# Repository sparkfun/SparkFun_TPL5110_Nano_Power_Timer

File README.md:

SparkFun TPL5110 Nano Power Timer
========================================

[*SparkFun Nano Power Switch (PRT-15353)*](https://www.sparkfun.com/products/15353)

Sometimes we want our projects on, but sometimes we want to turn them off for a while to save power. The SparkFun Nano Power Timer will run while only consuming minimal power (approximately 35nA) and turn your project on after a set amount of time. When you are done polling your sensors, posting data to the web, writing to your logger, or planning world domination, your microcontroller can tell the Nano Power Timer to turn off the power. No more running your microcontroller all day when you only want to read the ambient temperature once per hour.

Repository Contents
-------------------

* **/Documentation** - Data sheets, additional product information
* **/Firmware** - Example code 
* **/Hardware** - Eagle design files (.brd, .sch)
* **/Production** - Production panel files (.brd)

Documentation
--------------
* **[Hookup Guide](https://learn.sparkfun.com/tutorials/tpl5110-nano-power-timer-hookup-guide)** - Basic hookup guide for the TPL5110 Nano Power Timer.
* **[SparkFun Fritzing repo](https://github.com/sparkfun/Fritzing_Parts)** - Fritzing diagrams for SparkFun products.

License Information
-------------------
This product is _**open source**_! 

Please review the LICENSE.md file for license information. 

If you have any questions or concerns on licensing, please contact technical support on our [SparkFun forums](https://forum.sparkfun.com/viewforum.php?f=152).

Distributed as-is; no warranty is given.

- Your friends at SparkFun.

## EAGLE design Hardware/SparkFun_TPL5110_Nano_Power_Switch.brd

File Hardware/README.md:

SparkFun Nano Power Switch Design Files
=====================================

The .sch and .brd files hare are Eagle CAD schematic and PCB design files from SparkFun Electronics.
A freeware version of Eagle can be found [here](http://www.cadsoftusa.com/download-eagle/freeware/).

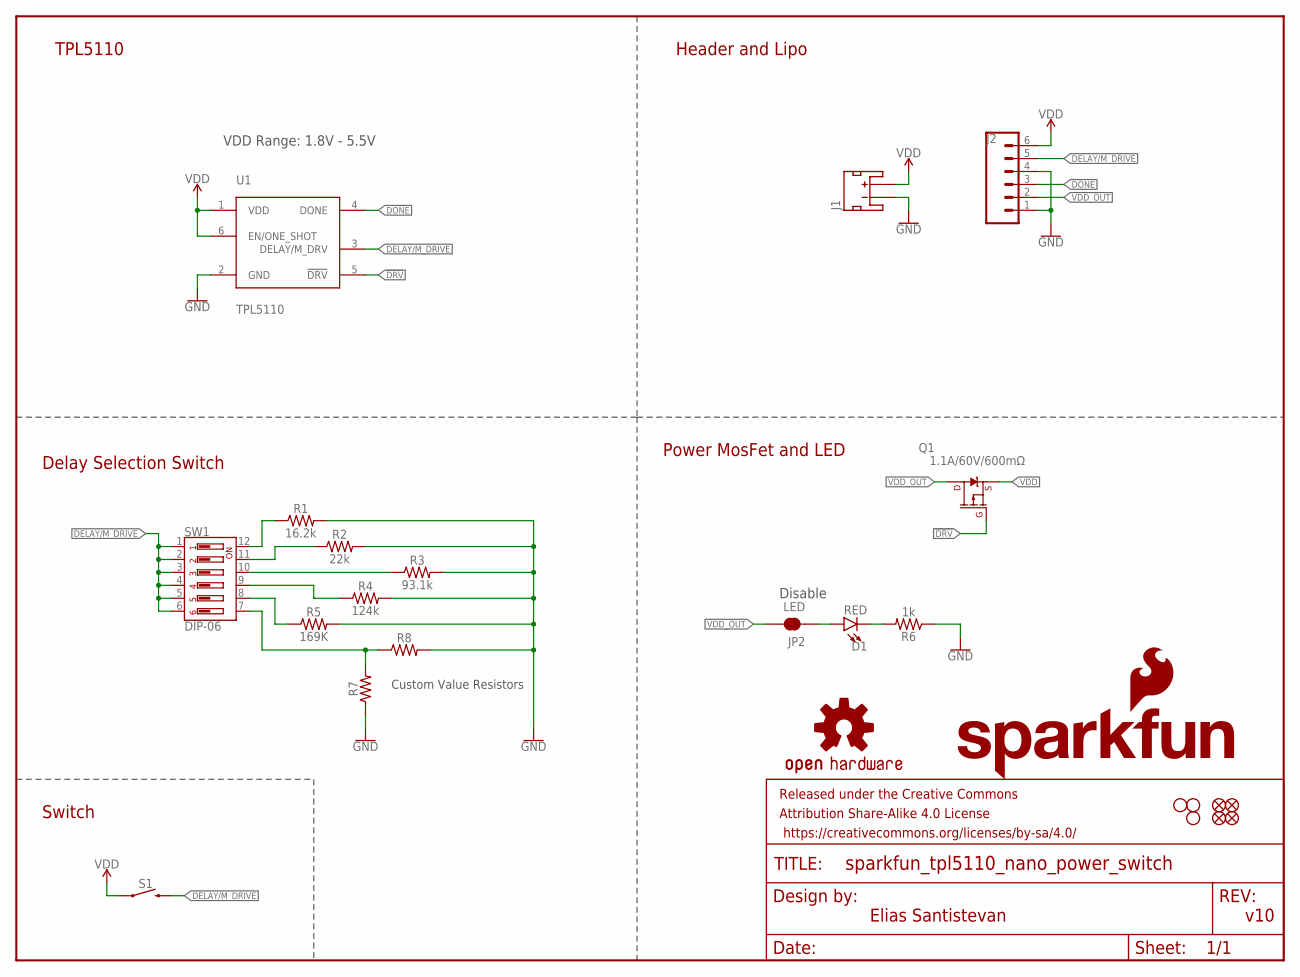
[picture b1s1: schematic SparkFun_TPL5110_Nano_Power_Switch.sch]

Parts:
D1: RED; LED-0603
FD1, FD2, FD3, FD4: FIDUCIALUFIDUCIAL; FIDUCIAL-MICRO
FRAME1: FRAME-LETTER; CREATIVE_COMMONS
H1, H2, H4: STAND-OFFTIGHT; STAND-OFF-TIGHT
J1: JST_2MM_MALE; JST-2-SMD
J2: CONN_06NO_SILK_NO_POP; 1X06_NO_SILK
JP2: LED; SMT-JUMPER_2_NC_TRACE_SILK
LOGO1: SFE_LOGO_NAME.1_INCH; SFE_LOGO_NAME_.1
LOGO2: OSHW-LOGOS; OSHW-LOGO-S
LOGO3: SFE_LOGO_FLAME.1_INCH; SFE_LOGO_FLAME_.1
Q1: 1.1A/60V/600mΩ; SOT23-3
R1: 16.2k; 0603
R2: 22k; 0603
R3: 93.1k; 0603
R4: 124k; 0603
R5: 169K; 0603
R6: 1k; 0603
R7: 0603
R8: AXIAL-0.3
S1: MOMENTARY-SWITCH-SPST-SMD-5.2MM-TALL; TACTILE_SWITCH_SMD_5.2MM
SW1: DIP-06; DIPSWITCH-06-SMD
U1: TPL5110; SOT23-6

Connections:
!DRV: Q1.1 (G), U1.5 (!DRV)
DELAY/M_DRIVE: J2.5, S1.3 (2), SW1.1, SW1.2, SW1.3, SW1.4, SW1.5, SW1.6, U1.3 (DELAY/M_DRV)
DONE: J2.3, U1.4 (DONE)
GND: J1.1 (-), J2.1, J2.4, R1.2, R2.2, R3.2, R4.2, R5.2, R6.1, R7.1, R8.P$2 (2), U1.2 (GND)
unnamed: D1.C, R6.2
unnamed: R1.1, SW1.12
unnamed: R2.1, SW1.11
unnamed: R3.1, SW1.10
unnamed: R4.1, SW1.9
unnamed: R5.1, SW1.8
unnamed: R7.2, R8.P$1 (1), SW1.7
unnamed: D1.A, JP2.1
VDD: J1.2 (+), J2.6, Q1.2 (S), S1.1, U1.1 (VDD), U1.6 (EN/ONE_SHOT)
VDD_OUT: J2.2, JP2.2, Q1.3 (D)

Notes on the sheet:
Elias Santistevan
v10
VDD Range: 1.8V - 5.5V
TPL5110
Header and Lipo
Power MosFet and LED
Delay Selection Switch
Switch
Disable
Custom Value Resistors

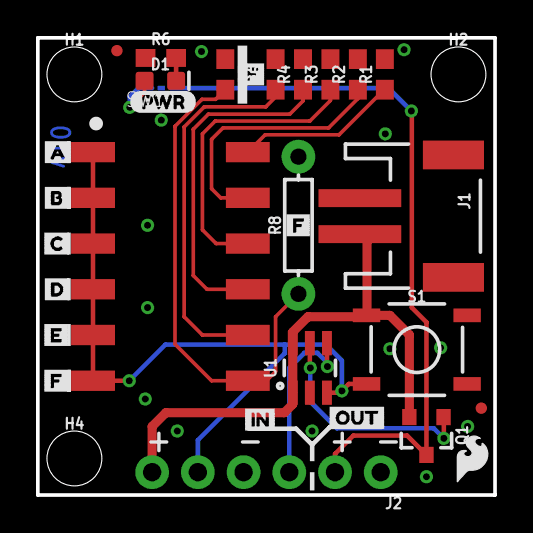
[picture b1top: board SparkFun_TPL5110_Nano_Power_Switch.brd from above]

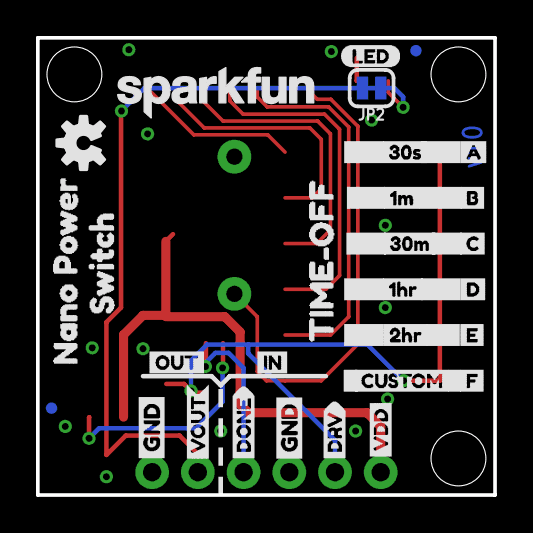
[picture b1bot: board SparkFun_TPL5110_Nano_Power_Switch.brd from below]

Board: 2 copper layers, 25.4 x 25.4 mm, 62 parts (29 on the bottom side), 14 nets.

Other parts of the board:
U$1: DONE0
U$2, U$4: GND-03
U$3: VOUT0
U$5: VDD0
U$6: NANO_POWER0
U$7: SWITCH0
U$8: 1M0
U$9: 30S4
U$10: 30M2
U$11: 1HR3
U$12: 2HR4
U$13: LED0
U$14: CUSTOM0
U$15: TIME#OFF0
U$16: DRV0
U$17, U$25: A0
U$18, U$26: B1
U$19, U$27: C2
U$20, U$28: D3
U$21, U$29: E4
U$22, U$23, U$24, U$30: F5
U$31, U$33: IN0
U$32, U$34: OUT1
U$35: PWR-()-03

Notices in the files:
parts and their libraries:
SparkFun-Aesthetics: Licensing: Creative Commons ShareAlike 4.0 International - https://creativecommons.org/licenses/by-sa/4.0
SparkFun-Aesthetics: Released under the Creative Commons Attribution Share-Alike 4.0 License
SparkFun-Aesthetics: https://creativecommons.org/licenses/by-sa/4.0
